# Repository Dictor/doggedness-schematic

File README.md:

# Doggedness (칠전팔기) ECU board

- [STM32 IOC](doggedness_schemetic.pdf)
- [PCB gerber](pcb.pdf)
- [Schematic](schematic.pdf)

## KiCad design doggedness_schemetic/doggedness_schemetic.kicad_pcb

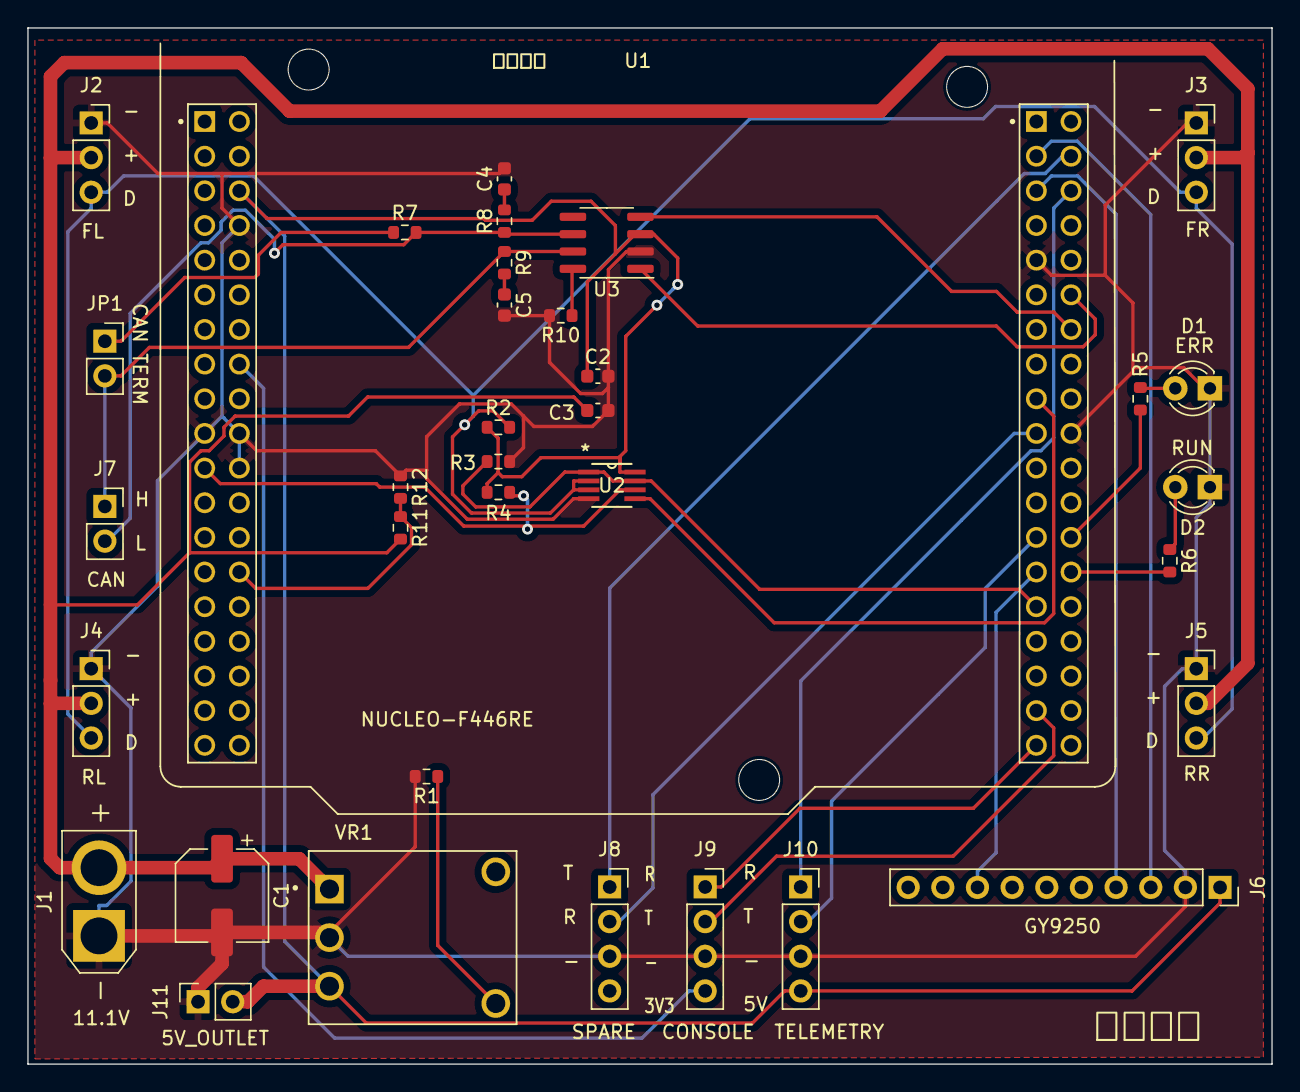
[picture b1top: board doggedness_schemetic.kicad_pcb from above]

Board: 2 copper layers, 91.2 x 75.9 mm, 35 parts (0 on the bottom side), 31 nets.

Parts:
C1: 100u; CP_Elec_6.3x7.7
C2, C3: 0.1u; C_0603_1608Metric
C4, C5: 560p; C_0603_1608Metric
D1: LED_ERR; LED_D3.0mm
D2: LED_RUN; LED_D3.0mm
J1: Conn_01x02; AMASS_XT30U-F_1x02_P5.0mm_Vertical
J2: MOTOR_FL; PinSocket_1x03_P2.54mm_Vertical
J3: MOTOR_FR; PinSocket_1x03_P2.54mm_Vertical
J4: MOTOR_RL; PinSocket_1x03_P2.54mm_Vertical
J5: MOTOR_RR; PinSocket_1x03_P2.54mm_Vertical
J6: GY-9250; PinSocket_1x10_P2.54mm_Vertical
J7: Screw_Terminal_01x02; PinSocket_1x02_P2.54mm_Vertical
J8: SPARE_UART; PinSocket_1x04_P2.54mm_Vertical
J9: CONSOLE_UART; PinSocket_1x04_P2.54mm_Vertical
J10: TELEMETRY_UART; PinSocket_1x04_P2.54mm_Vertical
J11: 5V_OUTLET; PinSocket_1x02_P2.54mm_Vertical
JP1: TERMINAL_R; PinSocket_1x02_P2.54mm_Vertical
R1: 348; R_0603_1608Metric
R2, R3, R4, R10: 10k; R_0603_1608Metric
R5, R6, R8, R9: 100; R_0603_1608Metric
R7: 120; R_0603_1608Metric
R11: 12k; R_0603_1608Metric
R12: 2.4k; R_0603_1608Metric
U1: NUCLEO-F446RE; MODULE_NUCLEO-F446RE
U2: 74LVC2G241DCTRE4; DCT8
U3: MCP2551-I-SN; SOIC-8_3.9x4.9mm_P1.27mm
VR1: PTH08080WAH; VREG_PTH08080WAH

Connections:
+3.3V: J9.4 (VCC), U1.CN7_16 (CN7_+3V3)
+5V: C2.1, J6.1 (VCC), J10.4 (VCC), J11.2 (+), R2.1, R4.1, U1.CN7_6 (E5V), U2.8 (VCC), U3.3 (VDD), VR1.3 (VO)
+BATT: C1.1, C3.1, J1.2 (+), J2.2 (VDD), J3.2 (VDD), J4.2 (VDD), J5.2 (VDD), R11.2, VR1.1 (VI)
CAN_RX: U1.CN10_14 (PA11), U3.4 (RXD)
CAN_TX: U1.CN10_12 (PA12), U3.1 (TXD)
GND: C1.2, C2.2, C3.2, C4.2, C5.2, D1.1 (K), D2.1 (K), J1.1 (-), J2.1 (GND), J3.1 (GND), J4.1 (GND), J5.1 (GND), J6.2 (GND), J8.3 (GND), J9.3 (GND), J10.3 (GND), J11.1 (-), R1.2, R3.2, R10.2, R12.1, U1.CN7_8 (CN7_GND), U1.CN7_19 (CN7_GND), U1.CN7_20 (CN7_GND), U1.CN7_22 (CN7_GND), U1.CN10_9 (CN10_GND), U1.CN10_20 (CN10_GND), U2.4 (GND), U3.2 (VSS), VR1.2 (GND)
GY_INT: J6.8 (INT), U1.CN10_27 (PB4)
GY_SCL: J6.3 (SCL), U1.CN10_3 (PB8)
GY_SDA: J6.4 (SDA), U1.CN10_5 (PB9)
LED_ERR: R5.2, U1.CN10_26 (PB15)
LED_RUN: R6.2, U1.CN10_28 (PB14)
MOTOR_RX: R4.2, U1.CN7_21 (PB7), U2.6 (1Y)
MOTOR_TX: U1.CN10_17 (PB6), U2.5 (2A)
MOTOR_TXE: R3.1, U1.CN10_29 (PB5), U2.1 (*1OE), U2.7 (2OE)
unnamed: C4.1, R8.2
unnamed: C5.1, R9.2
unnamed: D1.2 (A), R5.1
unnamed: D2.2 (A), R6.1
unnamed: J2.3 (DATA), J3.3 (DATA), J4.3 (DATA), J5.3 (DATA), R2.2, U2.2 (1A), U2.3 (2Y)
unnamed: J7.1 (CANH), JP1.2 (B), R9.1, U3.7 (CANH)
unnamed: J7.2 (CANL), R7.2, R8.1, U3.6 (CANL)
unnamed: J8.2 (RX), U1.CN10_19 (PC7)
unnamed: J8.1 (TX), U1.CN10_4 (PC6)
unnamed: J9.1 (RX), U1.CN10_37 (PA3)
unnamed: J9.2 (TX), U1.CN10_35 (PA2)
unnamed: J10.1 (RX), U1.CN10_6 (PC5)
unnamed: J10.2 (TX), U1.CN10_25 (PB10)
unnamed: JP1.1 (A), R7.1
unnamed: R11.1, R12.2, U1.CN7_28 (PA0)
unnamed: R10.1, U3.8 (Rs)
unnamed: R1.1, VR1.4 (VO_ADJ)

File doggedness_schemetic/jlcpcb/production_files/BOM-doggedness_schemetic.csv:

Comment,Designator,Footprint,LCSC
100u,C1,CP_Elec_6.3x7.7,C134220
10k,"R10,R2,R3,R4",R_0603_1608Metric,C15401
PTH08080WAH,VR1,VREG_PTH08080WAH,C181568
100,"R5,R6,R8,R9",R_0603_1608Metric,C22775
120,R7,R_0603_1608Metric,C22787
12k,R11,R_0603_1608Metric,C22790
2.4k,R12,R_0603_1608Metric,C22940
348,R1,R_0603_1608Metric,C23005
74LVC2G241DCTRE4,U2,DCT8,C2676069
0.1u,"C2,C3",C_0603_1608Metric,C3011705
560p,"C4,C5",C_0603_1608Metric,C376842
MCP2551-I-SN,U3,SOIC-8_3.9x4.9mm_P1.27mm,C49558
Conn_01x02,J1,AMASS_XT30U-F_1x02_P5.0mm_Vertical,C99101

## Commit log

2023-10-26 Complete prototype board
2023-10-27 Add copper pour
2023-10-27 Add README
